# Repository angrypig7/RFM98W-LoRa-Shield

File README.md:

# RFM98W LoRa Shield
RFM98W based arduino LoRa shield with SHT20 sensor for temperature/humidity monitoring, 0~60V analog voltage input terminal, connectors for 0.96" OLED display, Type-C port for power input

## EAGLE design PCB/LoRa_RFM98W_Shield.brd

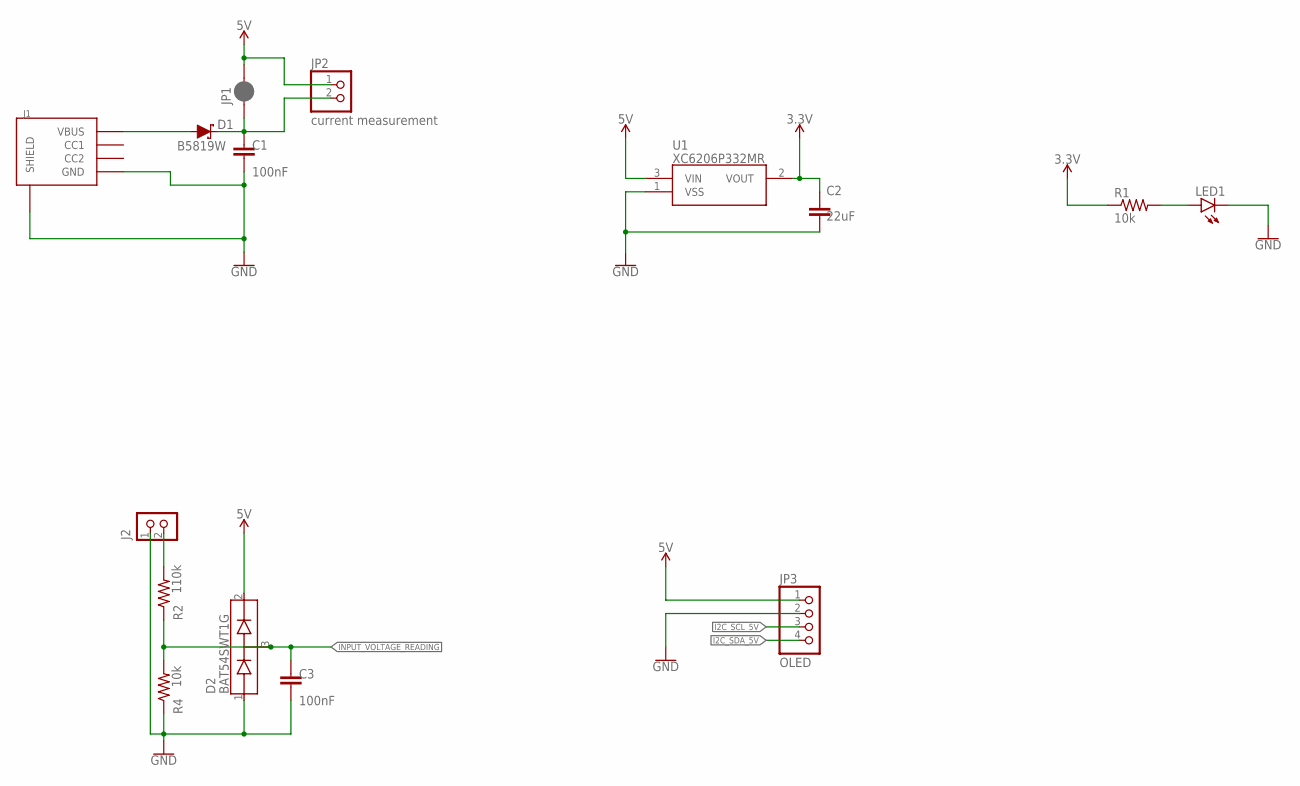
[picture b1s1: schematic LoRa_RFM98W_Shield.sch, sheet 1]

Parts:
C1, C3: 100nF; C0603
C2: 22uF; C0805
D1: B5819W; SOD-123
D2: BAT54SWT1G; SOT65P220X100-3N
J1: USB-TYPE-C-31-M-17
J2: CON_TERMINAL_BLOCK_02-5MM; TERMINAL_BLOCK_2P_5
JP1: JUMPER-SMT_2_NC_PASTE_SILK; SMT-JUMPER_2_NC_PASTE_SILK
JP2: current measurement; 1X02/OCT
JP3: OLED; 1X04/OCT
LED1: LEDCHIPLED_0805; CHIPLED_0805
R1, R4: 10k; R0603
R2: 110k; R0603
U1: XC6206P332MR; SOT95P280X130-3N

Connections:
3.3V: C2.2, R1.1, U1.2 (VOUT); also elsewhere on the board
5V: D2.2 (CATHODE), JP1.2, JP2.1, JP3.1, U1.3 (VIN); also elsewhere on the board
GND: C1.2, C2.1, C3.2, D2.1 (ANODE), J1.GND, J1.GND_2 (GND), J1.SHLD-B1 (SHIELD), J1.SHLD-B2 (SHIELD), J1.SHLD-B3 (SHIELD), J1.SHLD-B4 (SHIELD), J1.SHLD-T1 (SHIELD), J1.SHLD-T2 (SHIELD), J1.SHLD-T3 (SHIELD), J1.SHLD-T4 (SHIELD), J2.1, JP3.2, LED1.C, R4.1, U1.1 (VSS); also elsewhere on the board
I2C_SCL_5V: JP3.3; also elsewhere on the board
I2C_SDA_5V: JP3.4; also elsewhere on the board
INPUT_VOLTAGE_READING: C3.1, D2.3 (CATHODE-ANODE), R2.1, R4.2; also elsewhere on the board
unnamed: D1.A, J1.VBUS, J1.VBUS_2 (VBUS)
unnamed: LED1.A, R1.2
unnamed: J2.2, R2.2
unnamed: C1.1, D1.C, JP1.1, JP2.2

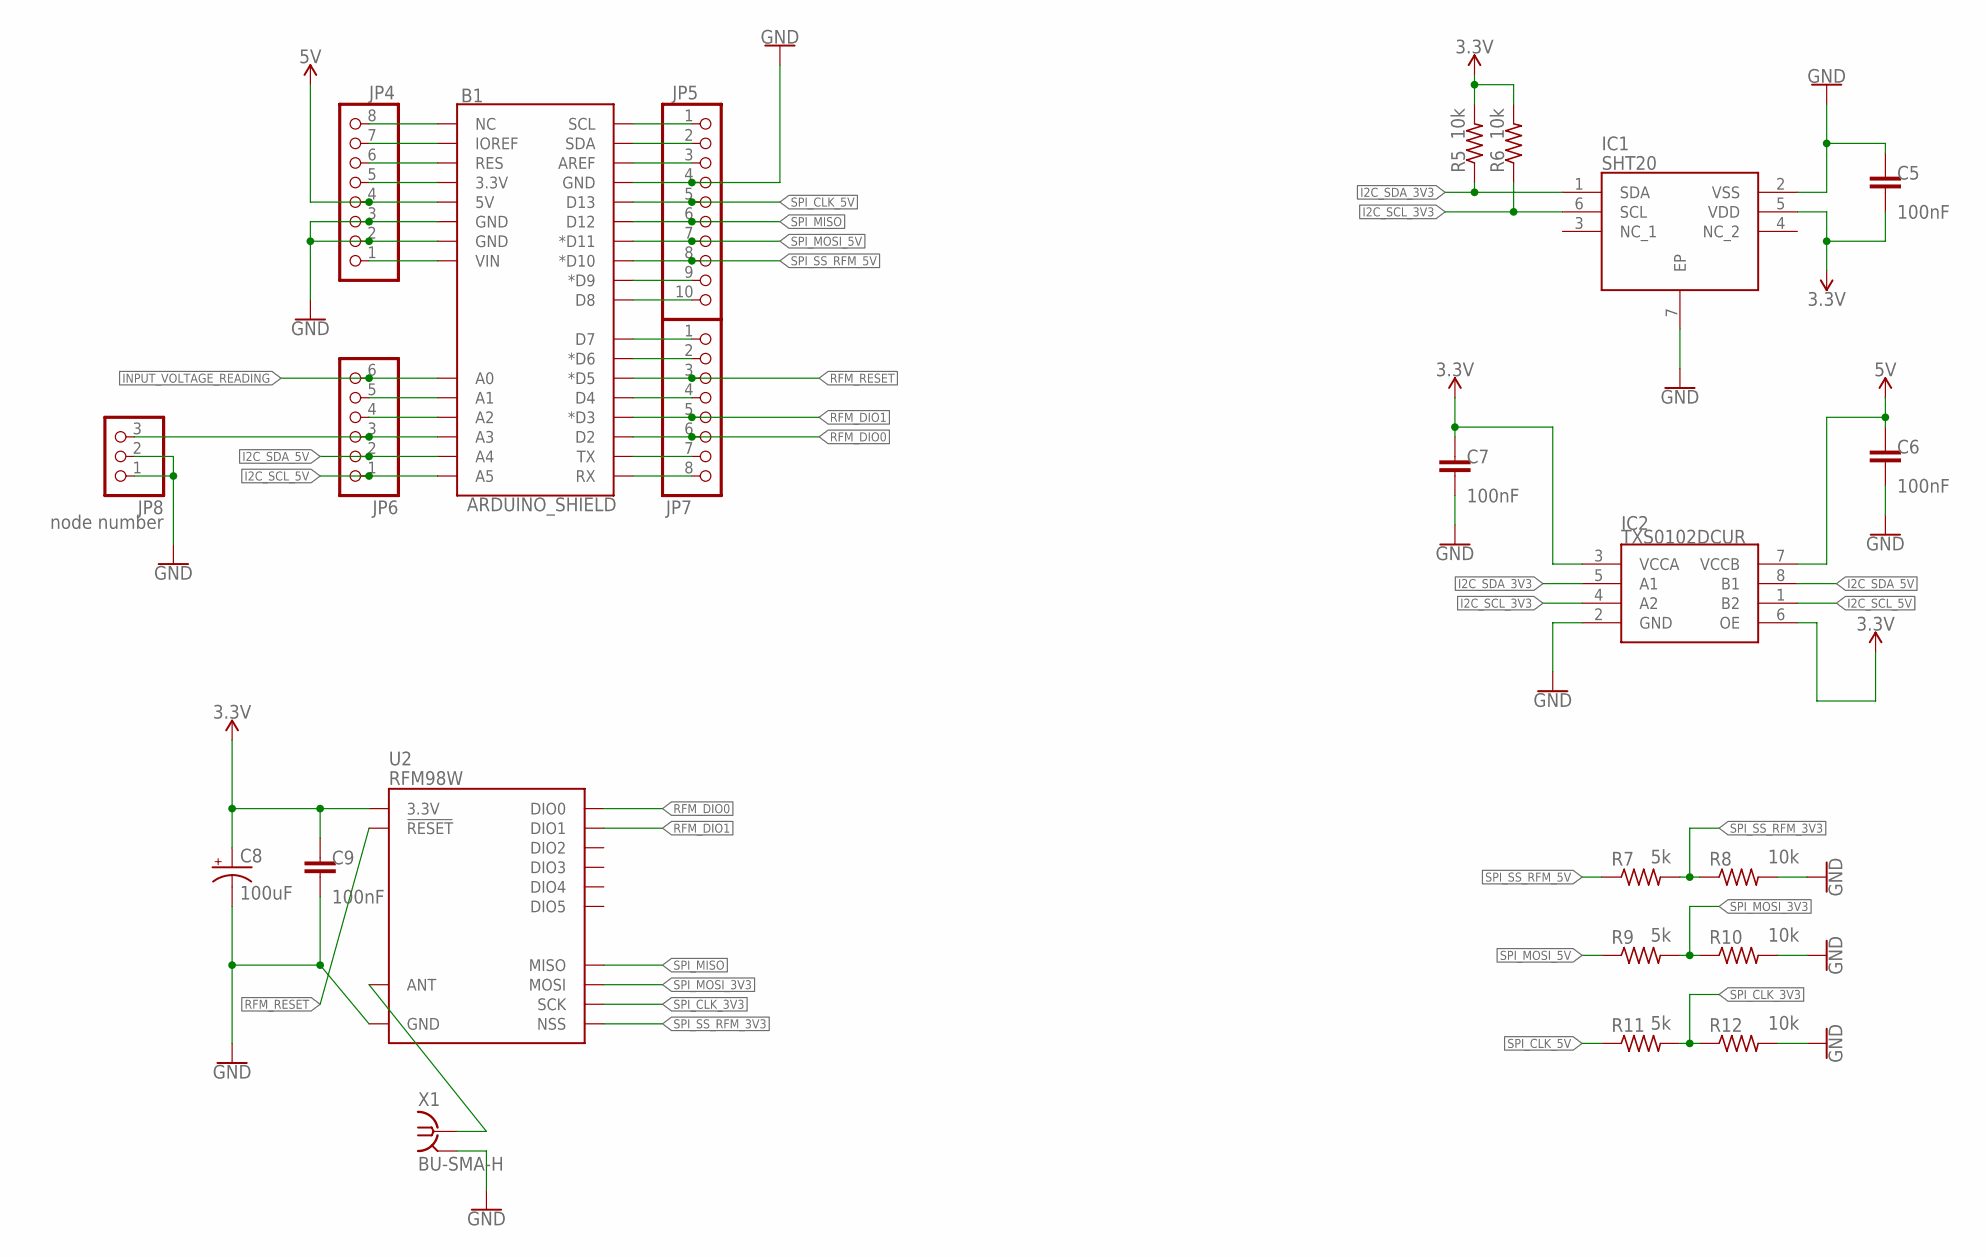
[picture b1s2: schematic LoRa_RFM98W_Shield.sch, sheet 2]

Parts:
B1: ARDUINO_SHIELD; UNO_R3_SHIELD_NOLABELS_LOCK
C5, C6, C7, C9: 100nF; C0603
C8: 100uF; SMC_B
IC1: SHT20; SON100P300X300X110-7N
IC2: TXS0102DCUR; SOP50P310X90-8N
JP4, JP7: PINHD-1X8/OCT; 1X08/OCT
JP5: PINHD-1X10/OCT; 1X10/OCT
JP6: PINHD-1X6/OCT; 1X06/OCT
JP8: node number; 1X03/OCT
R5, R6, R8, R10, R12: 10k; R0603
R7, R9, R11: 5k; R0603
U2: RFM98W; RFM95/96/97/98W
X1: BU-SMA-H

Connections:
3.3V: C5.2, C7.1, C8.+, C9.1, IC1.5 (VDD), IC2.3 (VCCA), IC2.6 (OE), R5.2, R6.2, U2.3.3V; also elsewhere on the board
5V: B1.5V, C6.1, IC2.7 (VCCB), JP4.4; also elsewhere on the board
GND: B1.GND@0 (GND), B1.GND@1 (GND), B1.GND@2 (GND), C5.1, C6.2, C7.2, C8.-, C9.2, IC1.2 (VSS), IC1.7 (EP), IC2.2 (GND), JP4.2, JP4.3, JP5.4, JP8.1, JP8.2, R8.2, R10.2, R12.2, U2.GND@1 (GND), U2.GND@2 (GND), U2.GND@3 (GND), X1.2, X1.3 (2), X1.4 (2), X1.5 (2); also elsewhere on the board
I2C_SCL_3V3: IC1.6 (SCL), IC2.4 (A2), R6.1
I2C_SCL_5V: B1.A5, IC2.1 (B2), JP6.1; also elsewhere on the board
I2C_SDA_3V3: IC1.1 (SDA), IC2.5 (A1), R5.1
I2C_SDA_5V: B1.A4, IC2.8 (B1), JP6.2; also elsewhere on the board
INPUT_RELAY_STATUS: B1.A1, JP6.5
INPUT_VOLTAGE_READING: B1.A0, JP6.6; also elsewhere on the board
unnamed: U2.ANT, X1.1
unnamed: B1.SCL, JP5.1
unnamed: B1.SDA, JP5.2
unnamed: B1.AREF, JP5.3
unnamed: B1.VIN, JP4.1
unnamed: B1.D4, JP7.4
unnamed: B1.D9 (*D9), JP5.9
unnamed: B1.D8, JP5.10
unnamed: B1.D7, JP7.1
unnamed: B1.D6 (*D6), JP7.2
unnamed: B1.TX, JP7.7
unnamed: B1.RX, JP7.8
unnamed: B1.3.3V, JP4.5
unnamed: B1.RES, JP4.6
unnamed: B1.IOREF, JP4.7
unnamed: B1.NC, JP4.8
unnamed: B1.A2, JP6.4
unnamed: B1.A3, JP6.3, JP8.3
RFM_DIO0: B1.D2, JP7.6, U2.DIO0
RFM_DIO1: B1.D3 (*D3), JP7.5, U2.DIO1
RFM_RESET: B1.D5 (*D5), JP7.3, U2.!RESET
SPI_CLK_3V3: R11.2, R12.1, U2.SCK
SPI_CLK_5V: B1.D13, JP5.5, R11.1
SPI_MISO: B1.D12, JP5.6, U2.MISO
SPI_MOSI_3V3: R9.2, R10.1, U2.MOSI
SPI_MOSI_5V: B1.D11 (*D11), JP5.7, R9.1
SPI_SS_RFM_3V3: R7.2, R8.1, U2.NSS
SPI_SS_RFM_5V: B1.D10 (*D10), JP5.8, R7.1

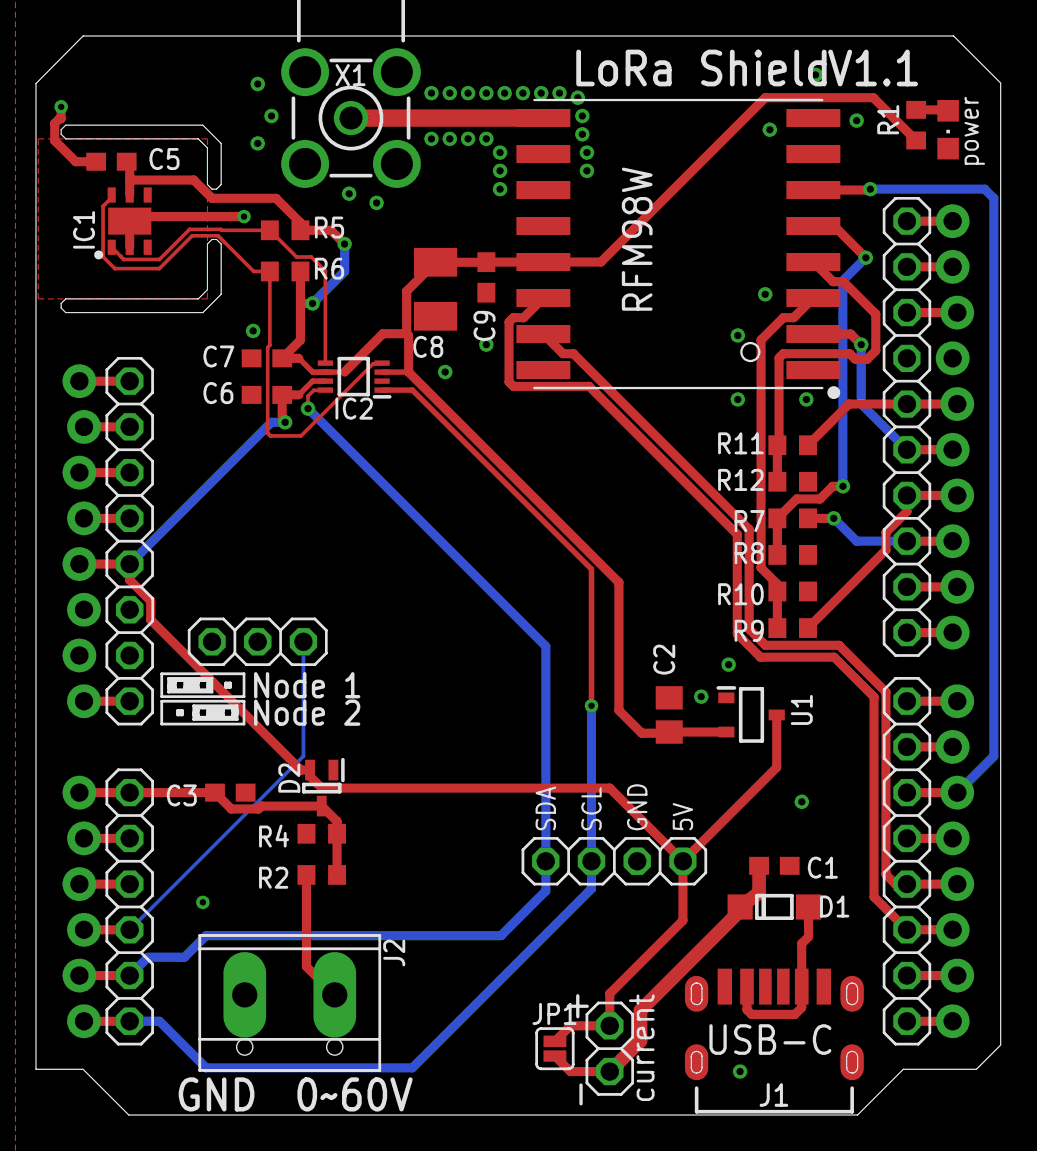
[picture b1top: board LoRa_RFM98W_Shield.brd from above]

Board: 2 copper layers, 53.6 x 59.9 mm, 38 parts (0 on the bottom side), 41 nets.

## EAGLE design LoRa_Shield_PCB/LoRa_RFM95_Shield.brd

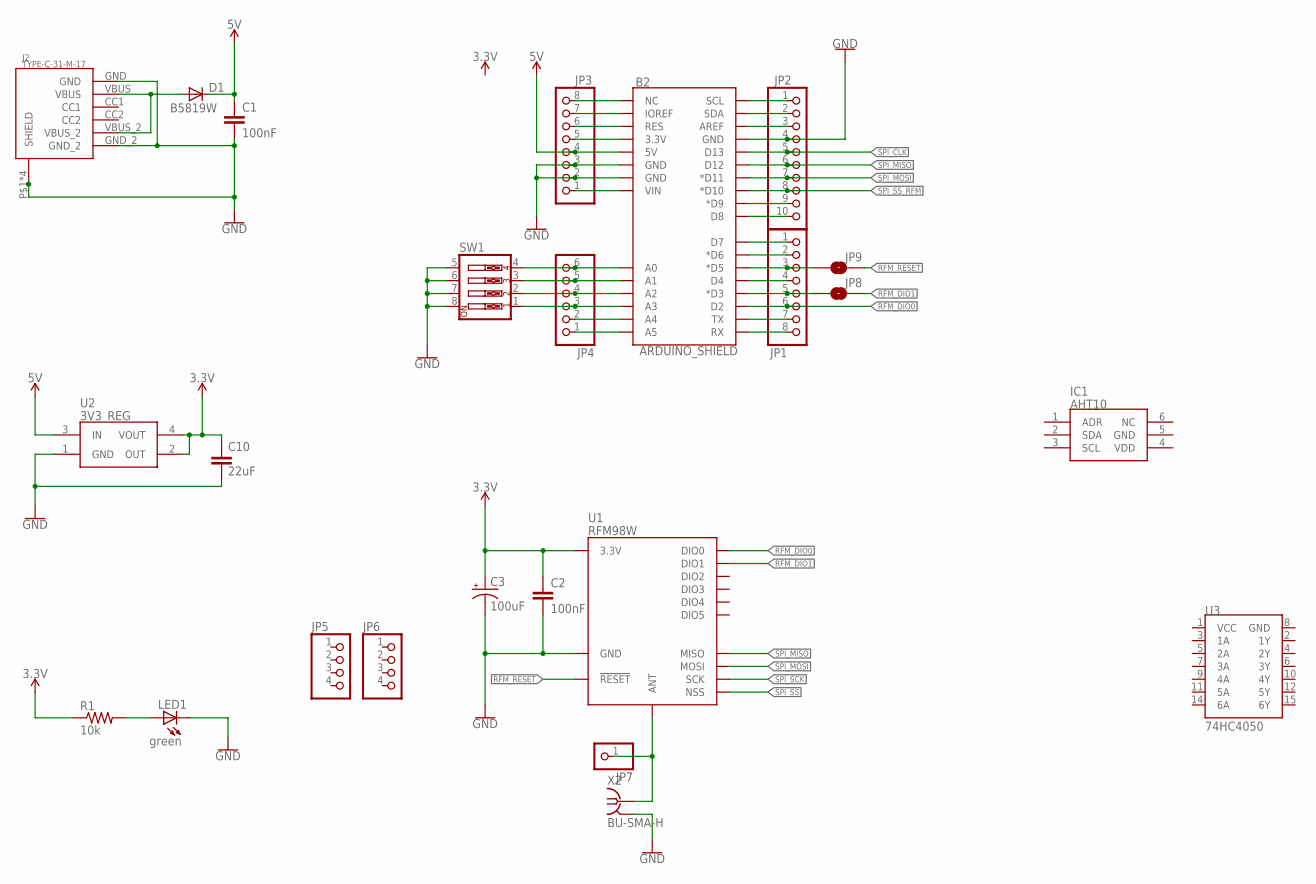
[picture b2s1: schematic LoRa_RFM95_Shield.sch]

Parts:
B2: ARDUINO_SHIELD; UNO_R3_SHIELD_NOLABELS_LOCK
C1, C2: 100nF; C0603
C3: 100uF; SMC_B
C10: 22uF; C0805
D1: B5819W; SOD-123
IC1: AHT10
J2: TYPE-C-31-M-17
JP1, JP3: PINHD-1X8/OCT; 1X08/OCT
JP2: PINHD-1X10/OCT; 1X10/OCT
JP4: PINHD-1X6/OCT; 1X06/OCT
JP5, JP6: PINHD-1X4/OCT; 1X04/OCT
JP7: PINHD-1X1/OCT; 1X01/OCT
JP8, JP9: JUMPER-SMT_2_NO_SILK; SMT-JUMPER_2_NO_SILK
LED1: green; CHIP-LED0603
R1: 10k; R0603
SW1: SW_DIP-4; EDG-04
U1: RFM98W; RFM95/96/97/98W
U2: 3V3_REG; SOT230P700X170-4N
U3: 74HC4050; SO16
X2: BU-SMA-H

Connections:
3.3V: C2.1, C3.+, C10.2, R1.1, U1.3.3V, U2.2 (OUT), U2.4 (VOUT)
5V: B2.5V, C1.1, D1.C, JP3.4, U2.3 (IN)
GND: B2.GND@0 (GND), B2.GND@1 (GND), B2.GND@2 (GND), C1.2, C2.2, C3.-, C10.1, J2.GND, J2.GND_2, J2.P$1 (SHIELD), J2.P$2 (SHIELD), J2.P$3 (SHIELD), J2.P$4 (SHIELD), JP2.4, JP3.2, JP3.3, LED1.C, SW1.5, SW1.6, SW1.7, SW1.8, U1.GND@1 (GND), U1.GND@2 (GND), U1.GND@3 (GND), U2.1 (GND), X2.2, X2.3 (2), X2.4 (2), X2.5 (2)
unnamed: D1.A, J2.VBUS, J2.VBUS_2
unnamed: JP7.1, U1.ANT, X2.1
unnamed: B2.SCL, JP2.1
unnamed: LED1.A, R1.2
unnamed: B2.SDA, JP2.2
unnamed: B2.AREF, JP2.3
unnamed: B2.VIN, JP3.1
unnamed: B2.D3 (*D3), JP1.5, JP8.1
unnamed: B2.D4, JP1.4
unnamed: B2.D5 (*D5), JP1.3, JP9.1
unnamed: B2.D9 (*D9), JP2.9
unnamed: B2.D8, JP2.10
unnamed: B2.D7, JP1.1
unnamed: B2.D6 (*D6), JP1.2
unnamed: B2.TX, JP1.7
unnamed: B2.RX, JP1.8
unnamed: B2.3.3V, JP3.5
unnamed: B2.RES, JP3.6
unnamed: B2.IOREF, JP3.7
unnamed: B2.NC, JP3.8
unnamed: B2.A0, JP4.6, SW1.4
unnamed: B2.A1, JP4.5, SW1.3
unnamed: B2.A2, JP4.4, SW1.2
unnamed: B2.A3, JP4.3, SW1.1
unnamed: B2.A4, JP4.2
unnamed: B2.A5, JP4.1
RFM_DIO0: B2.D2, JP1.6, U1.DIO0
RFM_DIO1: JP8.2, U1.DIO1
RFM_RESET: JP9.2, U1.!RESET
SPI_CLK: B2.D13, JP2.5
SPI_MISO: B2.D12, JP2.6, U1.MISO
SPI_MOSI: B2.D11 (*D11), JP2.7, U1.MOSI
SPI_SCK: U1.SCK
SPI_SS: U1.NSS
SPI_SS_RFM: B2.D10 (*D10), JP2.8

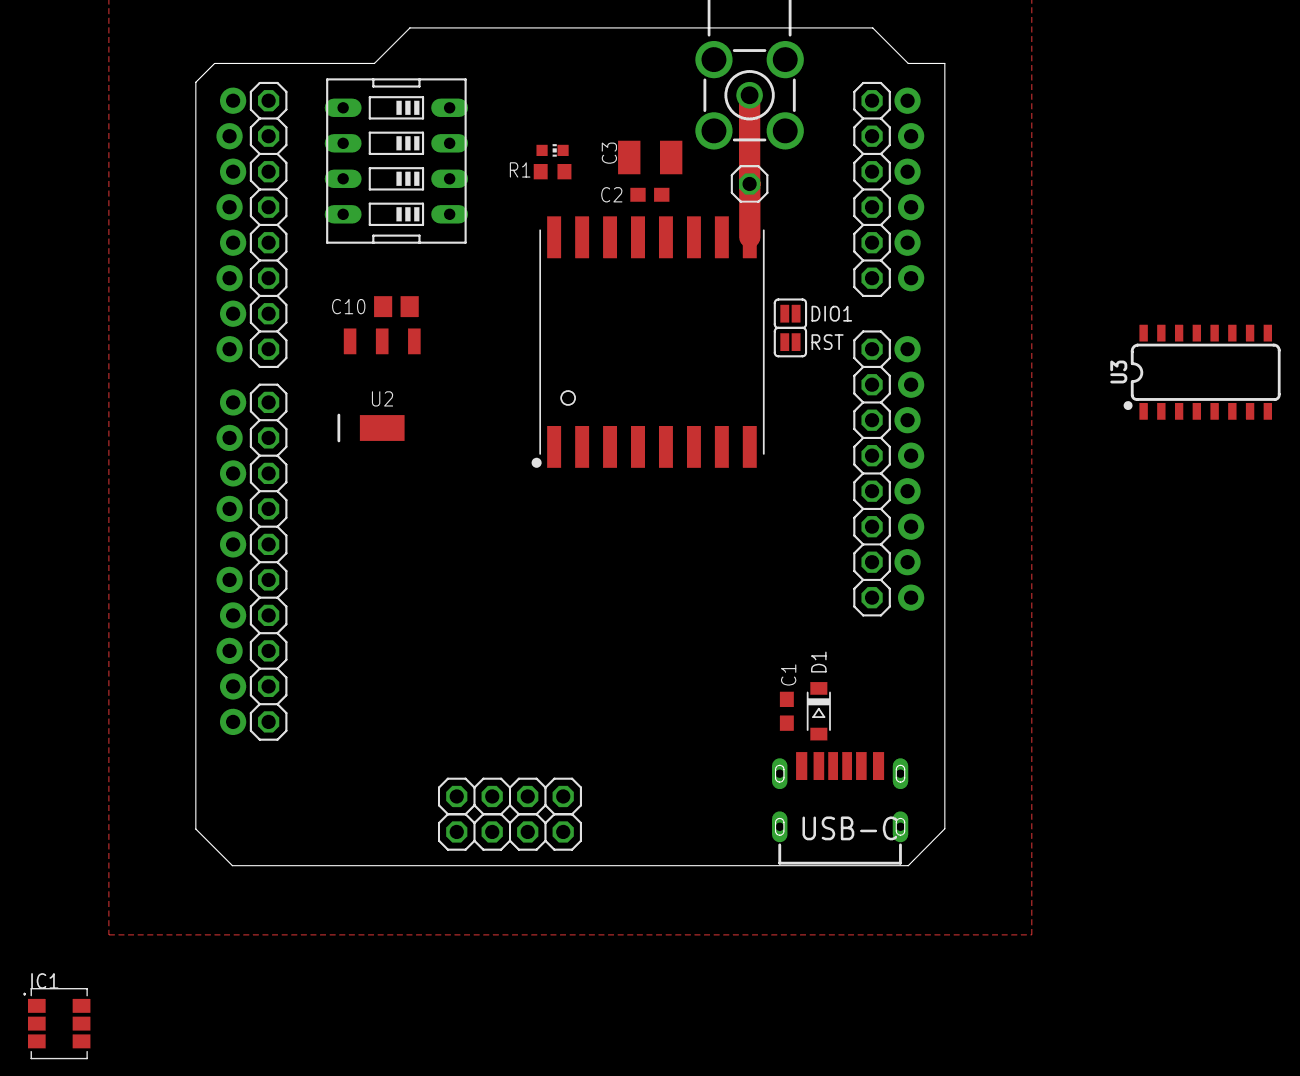
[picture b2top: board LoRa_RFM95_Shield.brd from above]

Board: 2 copper layers, 53.6 x 59.9 mm, 24 parts (0 on the bottom side), 36 nets.

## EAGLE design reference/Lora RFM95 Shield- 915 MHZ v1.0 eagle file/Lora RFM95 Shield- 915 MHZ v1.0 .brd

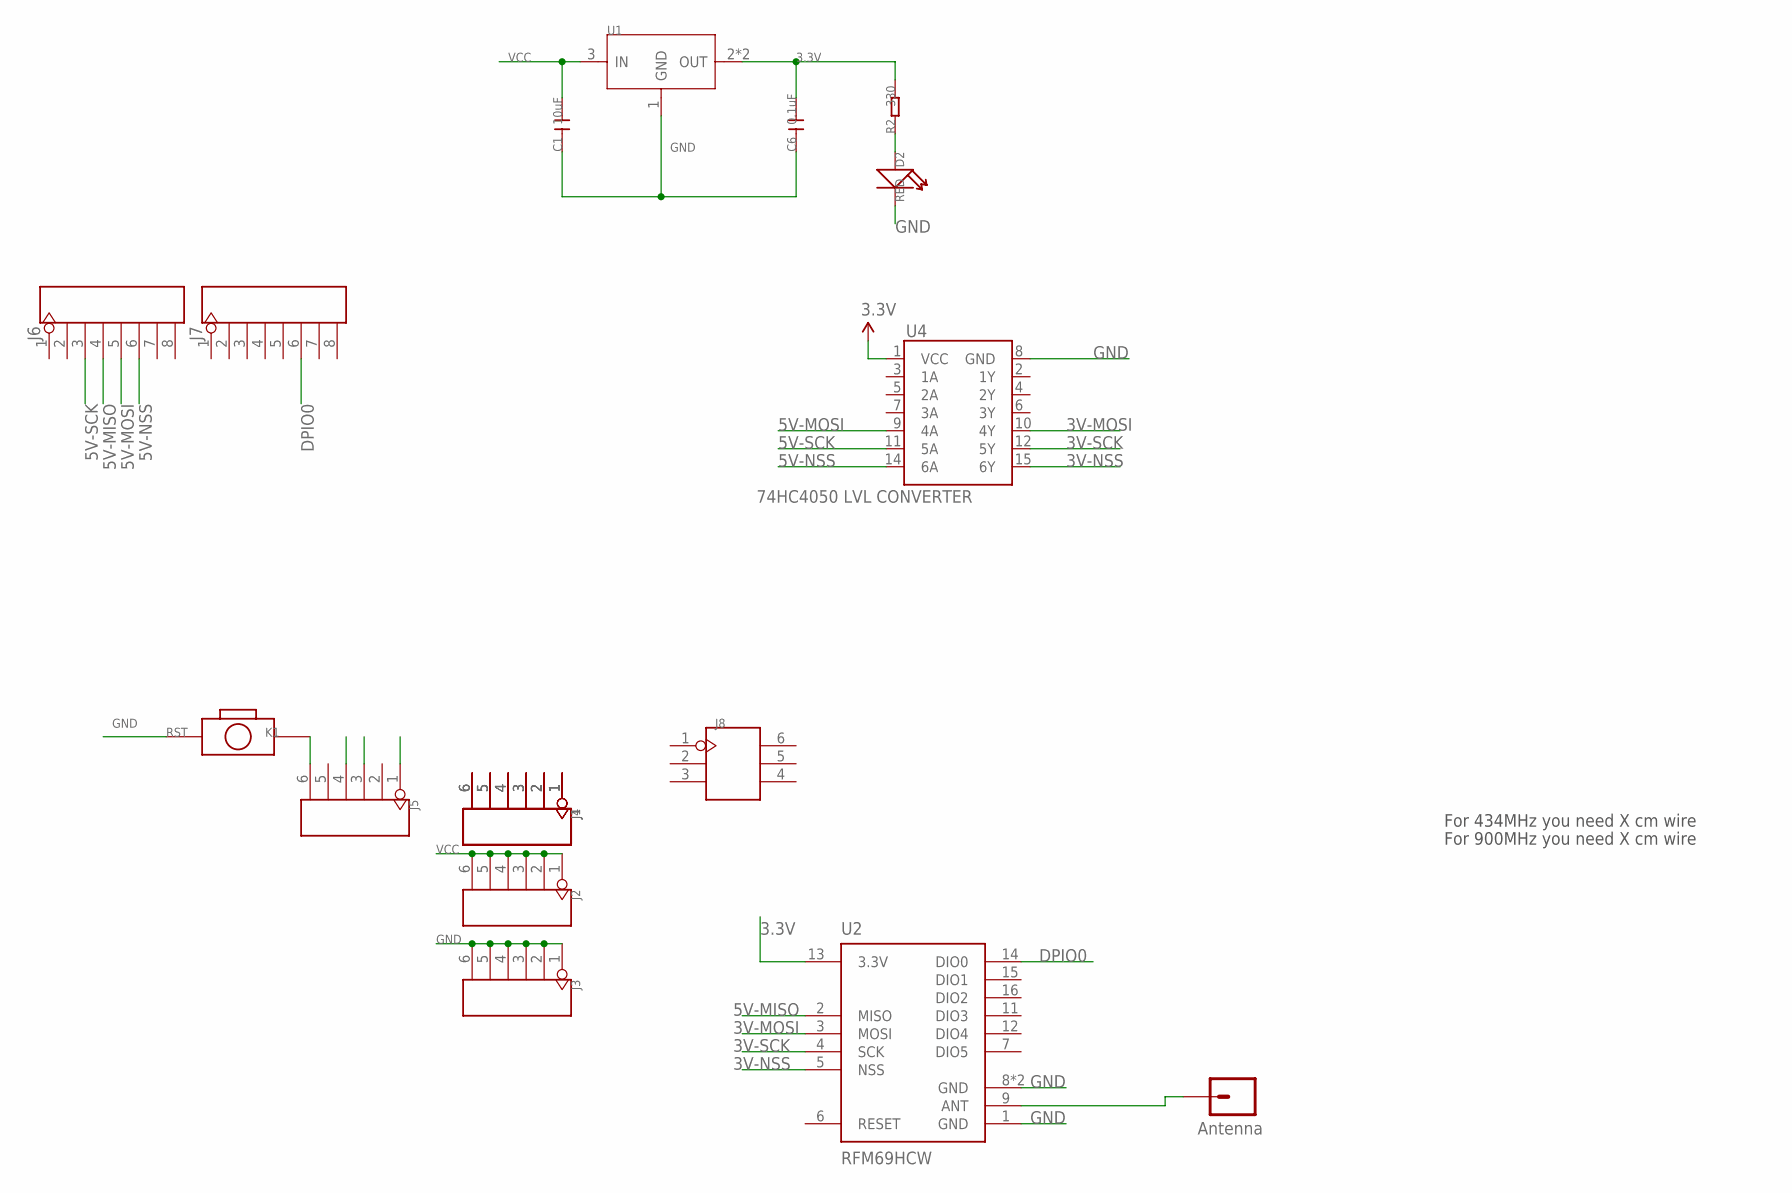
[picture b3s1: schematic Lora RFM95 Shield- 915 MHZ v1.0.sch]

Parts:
ANT: Antenna; 1X01
C1: 10uF; C0805
C6: 0.1uF; C0603
D2: RED; LED-0603
J1, J2, J3, J4, J5: HEADER-6P-65/35MIL; 6P-2.54-65/35MIL
J6, J7: HEADER-8P-65/35MIL; 8P-2.54-65/35MIL
J8: HEADER-2X3P-65/35MIL; 2X3P-2.54-65/35MIL
R2: 330; R0603
RST: K1; 2P-7.62X3.56-90D
U1: LD1117'SOT89'; SOT89
U2: RFM69HCW; RFM69HCW-XXXS2
U4: 74HC4050 LVL CONVERTER; SO016

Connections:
3.3V: C6.2, R2.2, U1.2 (OUT), U1.4 (OUT), U2.13 (3.3V), U4.1 (VCC)
3V-MOSI: U2.3 (MOSI), U4.10 (4Y)
3V-NSS: U2.5 (NSS), U4.15 (6Y)
3V-SCK: U2.4 (SCK), U4.12 (5Y)
5V-MISO: J6.4, U2.2 (MISO)
5V-MOSI: J6.5, U4.9 (4A)
5V-NSS: J6.6, U4.14 (6A)
5V-SCK: J6.3, U4.11 (5A)
DPIO0: J7.6, U2.14 (DIO0)
GND: C1.1, C6.1, D2.-, J3.1, J3.2, J3.3, J3.4, J3.5, J3.6, J5.3, RST.P$1 (1), U1.1 (GND), U2.1 (GND), U2.8 (GND), U2.10 (GND), U4.8 (GND)
unnamed: ANT.1, U2.9 (ANT)
unnamed: D2.+, R2.1
unnamed: J5.6, RST.P$2 (2)
PC0: J1.6, J4.6
PC1: J1.5, J4.5
PC2: J1.4, J4.4
PC3: J1.3, J4.3
PC4: J1.2, J4.2
PC5: J1.1, J4.1
VCC: C1.2, J2.1, J2.2, J2.3, J2.4, J2.5, J2.6, J5.4, U1.3 (IN)

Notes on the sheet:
For 434MHz you need X cm wire
For 900MHz you need X cm wire

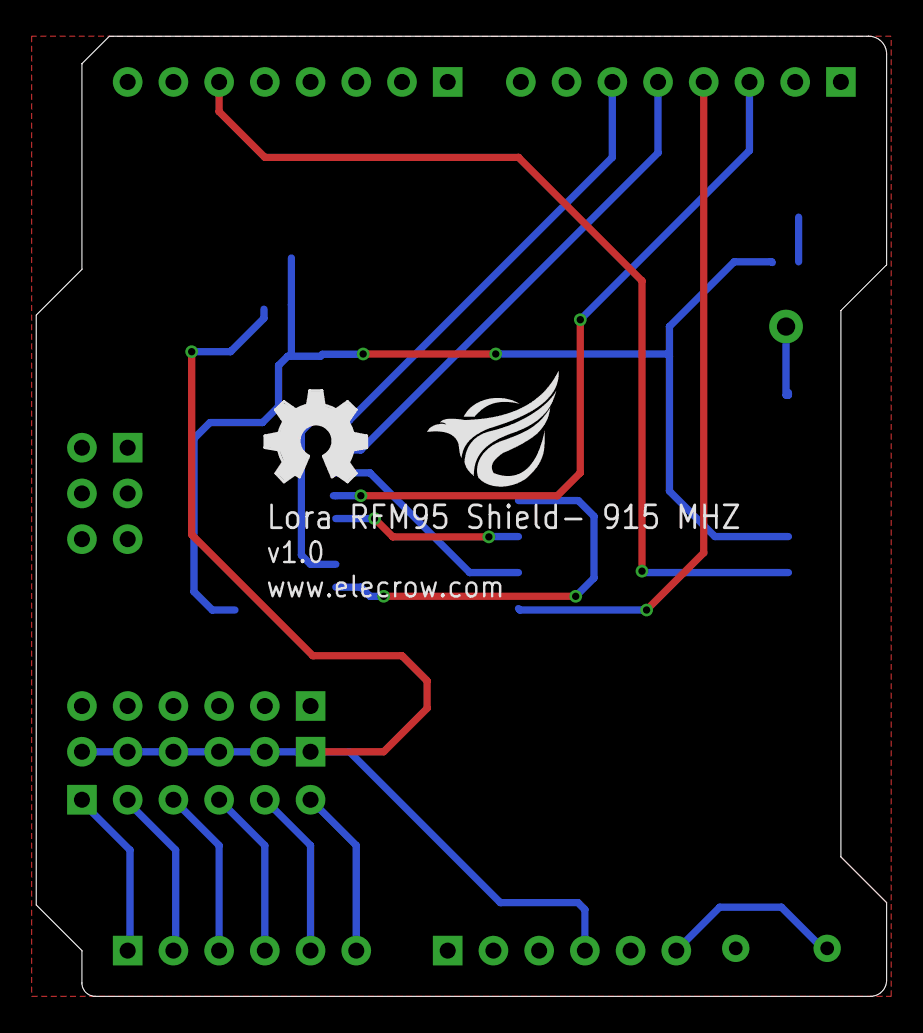
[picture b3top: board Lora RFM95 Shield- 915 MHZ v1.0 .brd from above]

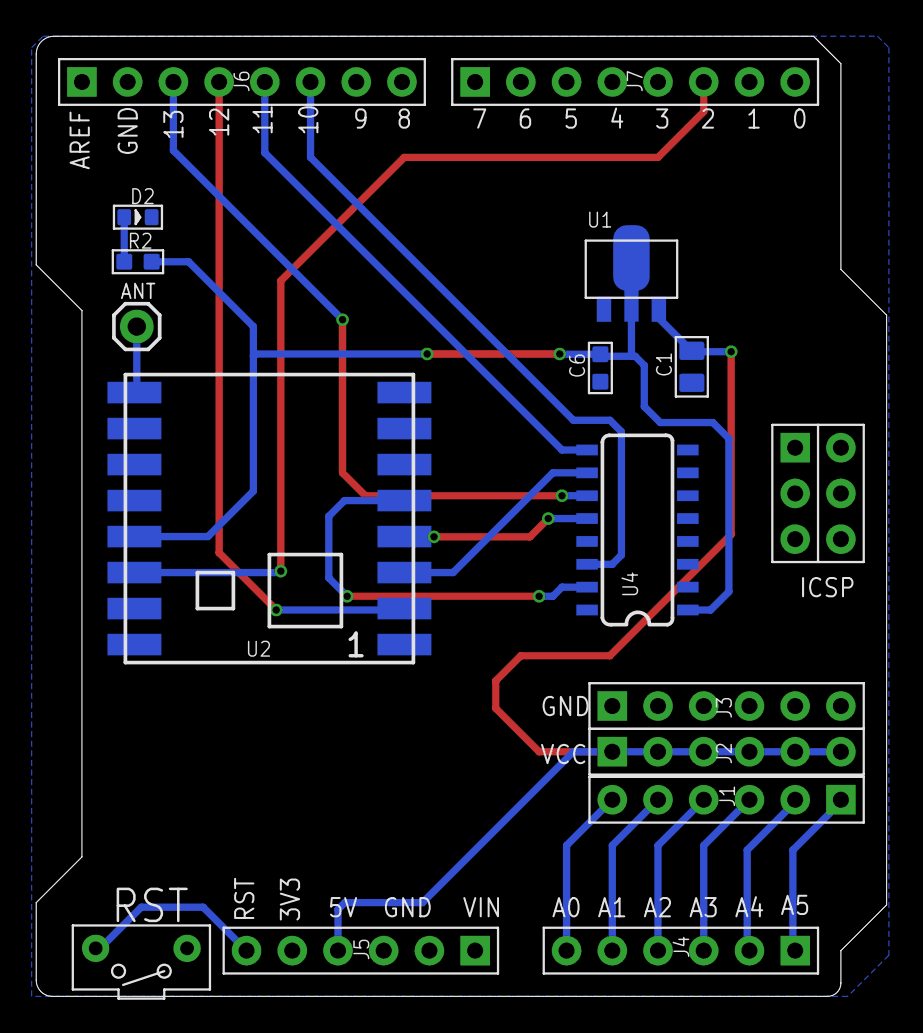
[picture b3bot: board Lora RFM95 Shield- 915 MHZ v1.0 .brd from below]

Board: 2 copper layers, 47.2 x 53.3 mm, 19 parts (17 on the bottom side), 20 nets.

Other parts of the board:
U$1: OSHW_FILLX200_NOTEXT
U$4: ELECROW_NRW_6

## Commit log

2019-12-22 gitignore
2019-12-22 added todo to README, added designs for reference
2019-12-23 project files added
2019-12-23 LoRa shield PCB power circuits
2019-12-25 PCB artwork started
2019-12-25 PCB outline
2019-12-26 PCB schematics almost complete, PCB layout partially done
2019-12-29 ADC circuit, new PCB layout
2020-01-01 layout update
2020-01-01 schematics, layout update
2020-01-02 PCB routing complete, RF impedance needs work
2020-01-02 RF feed line impedance fix, added version text
2020-01-02 output files updated
2020-01-02 parts updated for LCSC orders
2020-01-02 PCB production V1.0.0
2020-01-09 BOM update
2020-01-14 fixed copper pour, OLED orientation problem, optimized layout
2020-01-14 tx/rx code
2020-01-14 schematic resistor value, arduino code
2020-01-15 code update
2020-01-27 LoRa shield TX code update
2020-01-28 TX code optimization, RX code update
2020-01-28 final version with ACK from gateway - TX nodes cannot differentiate TX packet from ACK packet
2020-01-28 removed ACK function
2020-01-28 updated to latest
2020-02-11 added pictures
2020-04-15 cleanup & PCB minor update
2020-04-16 PCB minor update
2020-04-16 README
2020-04-16 compressed pics
2020-05-05 updated pics
2020-07-02 library update

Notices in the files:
parts and their libraries:
SparkFun-RF: Licensing: Creative Commons ShareAlike 4.0 International - https://creativecommons.org/licenses/by-sa/4.0
